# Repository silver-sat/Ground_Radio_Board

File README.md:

# Ground_Radio_Board
Silversat Ground Station Radio Board

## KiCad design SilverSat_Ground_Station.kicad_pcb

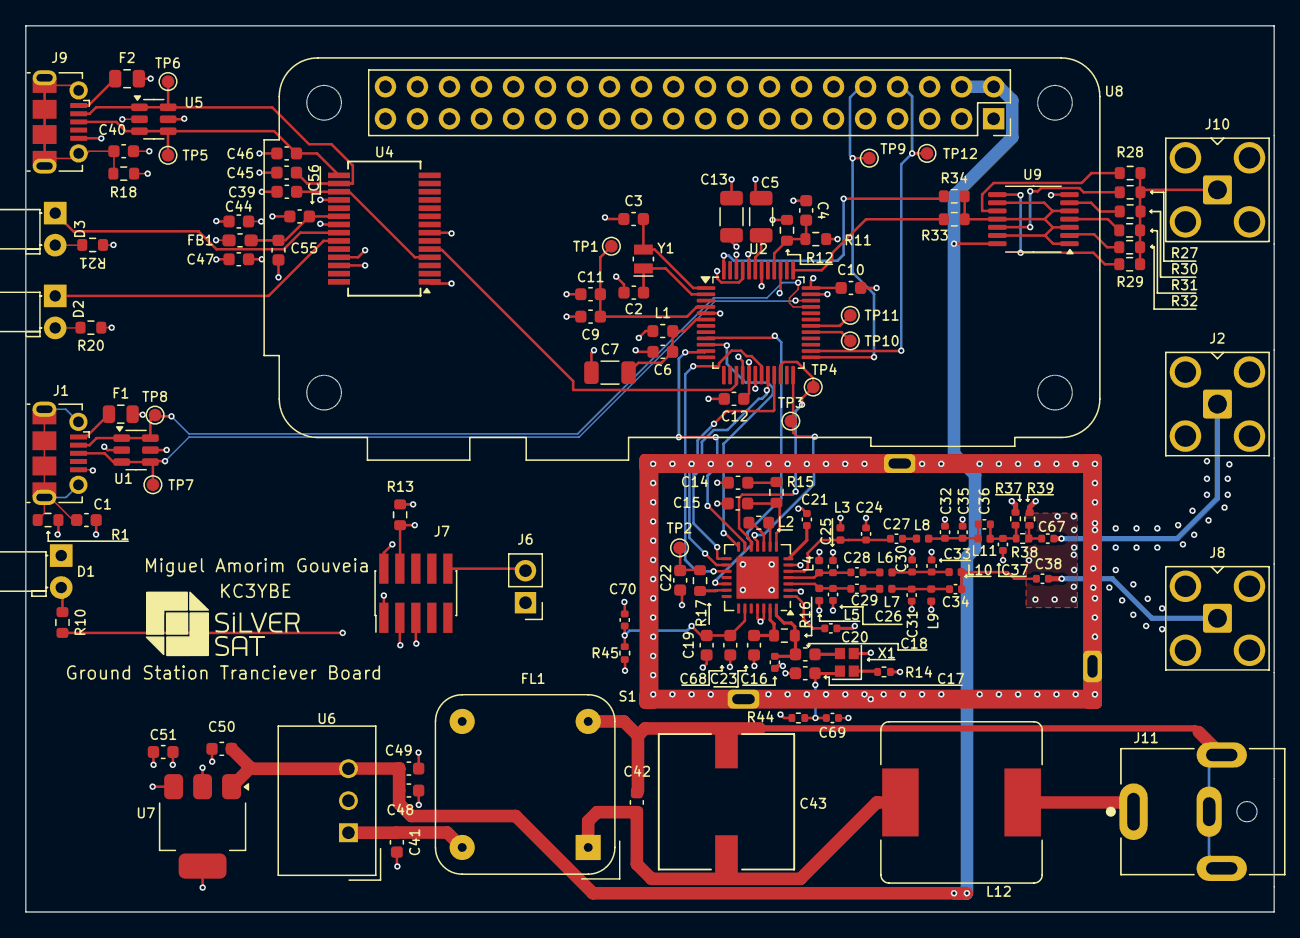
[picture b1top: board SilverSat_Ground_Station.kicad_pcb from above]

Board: 4 copper layers, 99.1 x 70.3 mm, 132 parts (0 on the bottom side), 86 nets.

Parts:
C1, C14, C17, C18, C23, C40, C49, C68: 0.01u; C_0603_1608Metric
C2, C3: 20p; C_0603_1608Metric
C4, C6, C9, C10, C12, C22, C56: 0.1u; C_0603_1608Metric
C5, C7, C13: 1u; C_1206_3216Metric
C11, C19, C55: 4.7u; C_0603_1608Metric
C15: 39p; C_0603_1608Metric
C16, C24, C25, C26, C35, C37, C69, C70: DNI; C_0402_1005Metric
C20, C21, C38, C67: 100p; C_0402_1005Metric
C27, C28, C29: 4.3p; C_0402_1005Metric
C30, C31, C32: 5.6p; C_0402_1005Metric
C33, C34: 5.1p; C_0402_1005Metric
C36: 6.8p; C_0402_1005Metric
C39: 100n; C_0603_1608Metric
C41: 10u; C_0603_1608Metric
C42: 4.7p; C_0603_1608Metric
C43: 470u; CAP_EEHZ-G16_PAN
C44, C47: 10n; C_0603_1608Metric
C45, C46: 47p; C_0603_1608Metric
C48: 22u; C_0603_1608Metric
C50: 0.22u; C_0603_1608Metric
C51: DNI; C_0603_1608Metric
D1, D2, D3: LED; LED_D3.0mm_Horizontal_O1.27mm_Z2.0mm
F1, F2: 300m; Fuse_0805_2012Metric
FB1: FerriteBead; L_0603_1608Metric_Pad1.05x0.95mm_HandSolder
FL1: Choke_Schaffner_RN102-0.6-02-4M4; Choke_Schaffner_RN102-04-14.0x14.0mm
J1, J9: USB_B_Micro; USB_Micro-B_Molex-105017-0001
J2, J8, J10: Conn_Coaxial; SMA_Amphenol_901-143_Horizontal
J6: 77315-801-02LF; PinHeader_1x02_P2.54mm_Vertical
J7: PinHeader_2x05_P1.27mm_Vertical_SMD
J11: PJ-063AH; CUI_PJ-063AH
L1: Ferrite Bead; L_0603_1608Metric
L2: 10n; L_0603_1608Metric
L3, L4, L5: 0.100u; L_0402_1005Metric
L6, L7, L8: 43n; L_0402_1005Metric
L9, L10: 27n; L_0402_1005Metric
L11: 4.7n; L_0402_1005Metric
L12: L_Small; L_Bourns_SRR1260
R1, R18: 1m; R_0603_1608Metric
R10: 931; R_0603_1608Metric
R11: 330; R_0603_1608Metric
R12, R13: 10k; R_0603_1608Metric
R14, R38, R44, R45: 0; R_0402_1005Metric
R15: 12k; R_0603_1608Metric
R16: 220; R_0603_1608Metric
R17: 100; R_0603_1608Metric
R20, R21: 270R; R_0603_1608Metric
R27, R28, R29, R30, R31, R32, R33, R34: 0; R_0603_1608Metric
R37, R39: DNI; R_0402_1005Metric
S1: MS353-10C_Masach_Shield; MS355-10_Masach_Shield
TP1: AREF; TestPoint_Pad_D1.0mm
TP2, TP3, TP4, TP9, TP10, TP11, TP12: TestPoint; TestPoint_Pad_D1.0mm
TP5: USB0_D+; TestPoint_Pad_D1.0mm
TP6: USB0_D-; TestPoint_Pad_D1.0mm
TP7: USB_D+; TestPoint_Pad_D1.0mm
TP8: USB_D-; TestPoint_Pad_D1.0mm
U1, U5: USBLC6-2SC6; SOT-23-6
U2: ATSAMD21G18A-A; TQFP-48_7x7mm_P0.5mm
U3: AX5043; QFN-28-1EP_5x5mm_P0.5mm_EP3.35x3.35mm
U4: FT232RL; SSOP-28_5.3x10.2mm_P0.65mm
U6: TSR1-2450E; Converter_DCDC_TRACO_TSR1-xxxxE_THT
U7: TL1963A-33DCYR; SOT-223
U8: RaspberryPiZero(v1.1); Raspberry_Pi_Zero_Socketed_THT_FaceDown_MountingHoles
U9: 74HC04; TSSOP-14_4.4x5mm_P0.65mm
X1: TG2016SMN; Crystal_SMD_2016-4Pin_2.0x1.6mm
Y1: CM8V-T1A-32.768KHZ-12.5PF-20PPM-TB-QA; Crystal_SMD_MicroCrystal_CC8V-T1A-2Pin_2.0x1.2mm

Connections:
3V3: C10.1, C12.1, C13.2, C51.1, J7.1, L1.1, R12.1, R13.1, R44.1, R45.1, U2.17 (VDDIO), U2.36 (VDDIO), U2.44 (VDDIN), U7.3 (OUT)
+5V: C48.1, C49.1, C50.1, U6.3 (Vout), U7.1 (IN), U8.2 (5vV_Power), U8.4 (5vV_Power), U9.14 (VCC)
+5V_USB: F1.2, U1.5 (VBUS)
+5V_USB2: C44.1, C47.1, F2.2, FB1.1, R20.1, R21.1, U5.5 (VBUS)
/AX5043/Attenuator/ATN_IN: C36.2, C37.1, L11.2, R37.2, R38.1
/AX5043/Attenuator/ATN_OUT: C67.1, R38.2, R39.2
/DATA: TP3.1, U2.24 (PA15), U3.11 (DATA)
/DCLK: TP4.1, U2.22 (PA13), U3.12 (DCLK)
/Driver/TR_Out: J10.1 (In), R27.2, R28.2, R29.2, R30.2, R31.2, R32.2
/IRQ: U2.9 (PA04), U3.19 (IRQ)
/MISO: U2.21 (PA12), U3.16 (MISO)
/MOSI: U2.19 (PB10), U3.17 (MOSI)
/PA: C67.2, J2.1 (In)
/PWRAMP: C22.1, R17.2, TP2.1
/Power_Supply/vin+: J11.1, L12.1
/Power_Supply/vin-: C42.2, C43.2, FL1.3, J11.2, J11.S1 (SHIELD), J11.S2 (SHIELD__1)
/RX: C38.2, J8.1 (In)
/RXD0: U2.15 (PA10), U4.5 (RXD)
/RXD1: TP9.1, U2.25 (PA16), U8.10 (BCM_15_(RxD))
/SAMD21/AREF: C9.1, C11.1, TP1.1, U2.4 (PA03)
/SAMD21/RX_LED_SWDIO: J7.2, U2.46 (PA31)
/SAMD21/RxD2: TP11.1, U2.30 (PA21)
/SAMD21/SWCLK: J7.4, R13.2, U2.45 (PA30)
/SAMD21/TXLED: R10.2, U2.39 (PA27)
/SAMD21/TxD2: TP10.1, U2.29 (PA20)
/SAMD21/X1: C3.2, U2.1 (PA00), Y1.2
/SAMD21/X2: C2.2, U2.2 (PA01), Y1.1
/SAMD21/~RESET: J6.2, J7.10, R11.2
/SCK: U2.20 (PB11), U3.15 (CLK)
/SYSCLK: U2.11 (PA06), U3.13 (SYSCLK)
/TXD0: U2.16 (PA11), U4.1 (TXD)
/TXD1: TP12.1, U2.26 (PA17), U8.8 (BCM_14_(TxD))
/TX/~RX: R33.1, U2.37 (PB22)
/USB0_D+: C46.2, J9.3 (D+), TP5.1, U4.15 (USBD+), U5.3 (I/O2), U5.4 (I/O2)
/USB0_D-: C45.2, J9.2 (D-), TP6.1, U4.16 (USBD-), U5.1 (I/O1), U5.6 (I/O1)
/USB_D+: J1.3 (D+), TP7.1, U1.3 (I/O2), U1.4 (I/O2), U2.34 (PA25)
/USB_D-: J1.2 (D-), TP8.1, U1.1 (I/O1), U1.6 (I/O1), U2.33 (PA24)
/~SEL: U2.10 (PA05), U3.14 (SEL)
/~TX/RX: R34.1, U2.48 (PB03)
GND: C1.2, C2.1, C3.1, C4.2, C5.2, C6.2, C7.1, C9.2, C10.2, C11.2, C12.2, C13.1, C14.2, C15.2, C16.1, C17.2, C19.1, C20.2, C21.2, C22.2, C23.1, C24.1, C25.1, C26.2, C30.1, C31.2, C32.2, C33.2, C35.2, C37.2, C39.1, C40.2, C41.2, C44.2, C45.1, C46.1, C47.2, C48.2, C49.2, C50.2, C51.2, C55.2, C56.1, C68.1, C69.1, C70.1, D1.1 (K), FL1.4, J1.5 (GND), J2.2 (Ext), J6.1, J7.3, J7.5, J8.2 (Ext), J9.5 (GND), J10.2 (Ext), L3.1, L4.1, L5.2, L9.2, R1.2, R14.1, R18.2, R37.1, R39.1, S1.1 (SHIELD), U1.2 (GND), U2.5 (GNDANA), U2.18 (GND), U2.35 (GND), U2.42 (GND), U3.2 (GND), U3.6 (GND), U3.25 (GPADC1), U3.26 (GPADC2), U3.29 (GND), U4.7 (GND), U4.18 (GND), U4.21 (GND), U4.25 (AGND), U4.26 (TEST), U5.2 (GND), U6.2 (GND), U7.2 (GND), U7.4 (GND), U8.6 (GND), U8.9 (GND), U8.14 (GND), U8.20 (GND), U8.25 (GND), U8.30 (GND), U8.34 (GND), U8.39 (GND), U9.7 (GND), X1.2 (GND)
unnamed: C14.1, R15.1
unnamed: C20.1, U3.1 (VDD_ANA)
unnamed: C21.1, U3.7 (VDD_ANA)
unnamed: C27.2, L8.2
unnamed: C28.2, L6.1
unnamed: C29.1, L7.1
unnamed: C30.2, C33.1, L6.2, L10.1
unnamed: C31.1, C34.2, L7.2, L9.1
unnamed: C32.1, C35.1, C36.1, L8.1, L11.1
unnamed: C34.1, C38.1, L10.2
unnamed: C42.1, C43.1, FL1.1, L12.2
unnamed: D1.2 (A), R10.1
unnamed: D2.2 (A), R20.2
unnamed: D2.1 (K), U4.23 (CBUS0)
unnamed: D3.2 (A), R21.2
unnamed: D3.1 (K), U4.22 (CBUS1)
unnamed: C1.1, J1.6 (Shield), R1.1
unnamed: F1.1, J1.1 (VBUS)
unnamed: C40.1, J9.6 (Shield), R18.1
unnamed: F2.1, J9.1 (VBUS)
unnamed: R27.1, U9.12
unnamed: R28.1, U9.10
unnamed: R29.1, U9.8
unnamed: R30.1, U9.6
unnamed: R31.1, U9.4
unnamed: R32.1, U9.2
unnamed: R33.2, R34.2, U9.1, U9.3, U9.5, U9.9, U9.11, U9.13
unnamed: C6.1, C7.2, L1.2, U2.6 (VDDANA)
unnamed: C5.1, U2.43 (VDDCORE)
unnamed: C4.1, R11.1, R12.2, U2.40 (~RESET)
unnamed: C25.2, C28.1, L4.2, U3.4 (ANTN)
unnamed: C24.2, C27.1, L3.2, U3.5 (ANTP1)
unnamed: C26.1, C29.2, L5.1, U3.3 (ANTP)
unnamed: C23.2, R16.2, U3.27 (CLK16N)
unnamed: C16.2, C18.2, R16.1, U3.28 (CLK16P)
unnamed: C15.1, R15.2, U3.8 (FILT)
unnamed: L2.2, U3.10 (L1)
unnamed: L2.1, U3.9 (L2)
unnamed: R17.1, U3.20 (PWRAMP)
unnamed: C19.2, C68.2, C70.2, R45.2, U3.23 (VDD_IO)
unnamed: C39.2, U4.4 (VCCIO), U4.17 (3V3OUT)
unnamed: C55.1, C56.2, FB1.2, U4.20 (VCC)
unnamed: C41.1, FL1.2, U6.1 (Vin)
unnamed: C18.1, X1.3 (OUT)
unnamed: R14.2, X1.1 (VC)
unnamed: C17.1, C69.2, R44.2, X1.4 (VDD)

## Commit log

2024-03-09 Update README.md
    First commit
2024-03-13 test commit
    test of a directory commit
2024-03-13 Revert "test commit"
    This reverts commit 4f2e8a94b08165137c73e908ad9e4bbcec684a32.
2024-03-13 ignoring .lck
    ignoring lock files
2024-03-13 Update .gitignore
    Fixed the ignore definition
2024-04-20 Second attempt at first commit
2024-06-08 Started PCB design
2024-06-08 Continued PCB work
2024-06-15 Worked on the driver layout
2024-06-15 Finished micro usb ports & continued PCB design
2024-06-22 Worked on better layout and cleaned up some traces
2024-07-20 Finished general design & cleaned up
2024-08-03 minor fixes and additions
    added 3d bodies to RF connectors, USB connectors and power connector.
    Fixed vias attached to wrong net under Ax5043
2024-08-03 added 3d models to connectors
    I also fixed a couple of DRC errors and adjusted the design rules and stackup to match what Oshpark is using right now.
2024-08-03 Update SilverSat_Ground_Station.kicad_pcb
    added RPi. We'll need to add a connector (socket header) to raise it up
2024-08-04 New step file and board dimensions
    I had to modify the board dimensions to fit the case. I also had to move one of the RF connectors to get it out of the wall. They're spaced okay now. The panel design is based on this spacing, so if 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
2024-08-07 Modified schematics and placement
    I removed some hardware that we were not really using to simplify the routing. I also swapped pins on the usb protectors for the same reason. I modified some components either to give them a real par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
    I then moved the connectors to simplify routing as well, and moved a couple of blocks (nice work Miguel in putting the right parts into groups).
    Finally, I completed the design of the supply input filter. It's probably overkill, but can't hurt (even though the parts are huge!)
2024-08-08 mentor version
    Has a few minor changes from the version on main. Mostly rip ups of existing routes to make the routing cleaner. I also created space in the RF chain to make room so I could put the silk screen in be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
2024-08-10 Added header
    Added header on front panel that has 12V, Ground and 2 spare io signals.
2024-08-10 extra header
    Added some more signals to the extra header. Also added a nice big ground square.
2024-08-11 part values and design correction
    Just noticed that TX/RX were not swapped on any serial interface. Fixed that.
    Also added MPN and manufacturer to a bunch of parts and ordered them.
2024-08-23 Schematic wasn't saved, so it didn't get modified in repo
    Fixing this...it passes DRC
2024-08-24 Worked on the pcb routing
2024-08-27 packaging files
    files to make labels for the box
2024-08-27 fixed crossovers, IO voltage and regulator part number
    Fixed crossovers on serial ports.
    Fixed IO voltage on FT232RL. IO Voltage needs to be 3V3.
    Fixed regulator part number. Part was 1.5V out, needs to be 3V3.
2024-08-31 Fixed SAMD21 3V3 & continued routing
    The SAMD21's 3V3 was on /SAMD21/3V3, but is now on 3V3.
2024-09-07 Finished general routing & started fixing errors
    Finished non 5V routing (still needs to be refined) and began working through DRC violations
2024-09-14 Cleaned up
2024-09-21 Finished Complete Design
    I just finished up the (hopefully) final design of the Ground Station transceiver. The board should now be ready to be reviewed before being bought.
2024-09-28 Final Touches
    Fixed some DRC Errors and cleaned up some of the routing. Ground Station is now completely ready for review (finally).
2024-10-05 Board Modifications After Review
    Board was reviewed and necessary modifications have been made.
2024-10-05 Changed PI model path
    I realized that the PI model path was local, so I quickly changed it to work with any computer.
2024-10-12 Finished Twice Reviewed Board Issues, And Fixed All Silkscreen.
    Finished all feedback from the second review, and gave (hopefully) everything a silkscreen version of their part number and moved them to a good location.
2024-10-12 Added SilverSat Logo and My Name
2024-10-22 upload of package design
    package design image
2024-11-06 Paste layer for stencil
    Gerber for stencil
2024-11-06 Create SilverSat_Ground_Station-job.gbrjob
    And job file
